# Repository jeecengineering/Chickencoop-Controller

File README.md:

# Chickencoop-Controller
Chickencoop controller (inactive)

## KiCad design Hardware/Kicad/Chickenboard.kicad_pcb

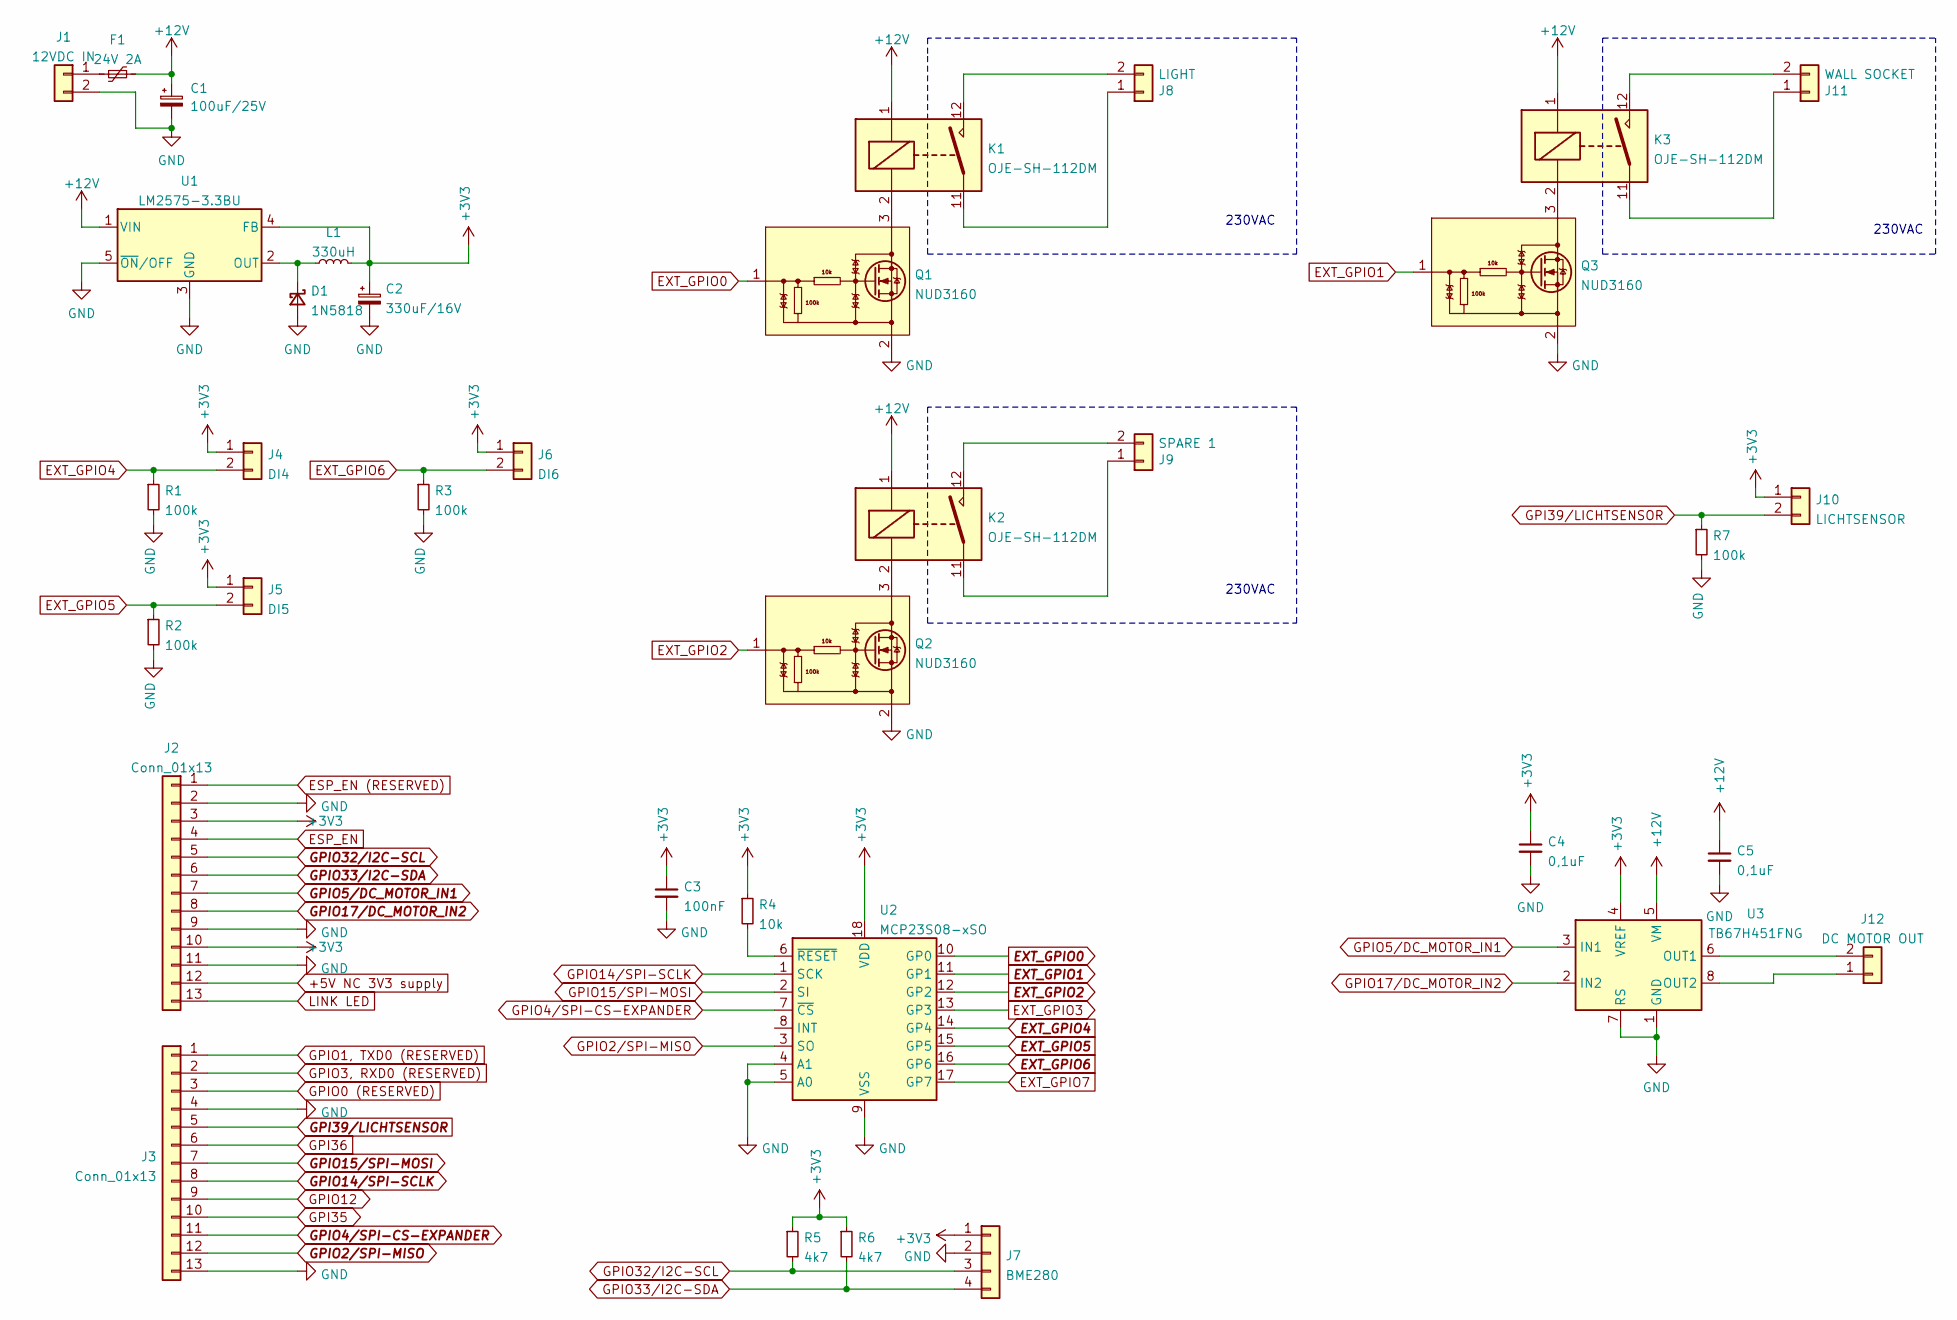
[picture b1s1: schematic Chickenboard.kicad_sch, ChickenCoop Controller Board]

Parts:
C1: 100uF/25V; CP_Radial_D8.0mm_P5.00mm
C2: 330uF/16V; CP_Radial_D8.0mm_P3.50mm
C3: 100nF; C_0805_2012Metric_Pad1.18x1.45mm_HandSolder
C4, C5: 0,1uF; C_0805_2012Metric_Pad1.18x1.45mm_HandSolder
D1: 1N5818; D_DO-41_SOD81_P10.16mm_Horizontal
F1: 24V 2A; Fuse_2920_7451Metric_Pad2.10x5.45mm_HandSolder
J1: 12VDC IN; TerminalBlock_CUIDevices_TB004_508-1x02_P5.08mm_Horizontal
J2, J3: Conn_01x13; PinSocket_1x13_P2.54mm_Vertical
J4: DI4; TerminalBlock_CUIDevices_TB004_508-1x02_P5.08mm_Horizontal
J5: DI5; TerminalBlock_CUIDevices_TB004_508-1x02_P5.08mm_Horizontal
J6: DI6; TerminalBlock_CUIDevices_TB004_508-1x02_P5.08mm_Horizontal
J7: BME280; TerminalBlock_CUIDevices_TB004_508-04BE-1x04_P5.08mm_Horizo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
J8: LIGHT; TerminalBlock_CUIDevices_TB004_508-1x02_P5.08mm_Horizontal
J9: SPARE 1; TerminalBlock_CUIDevices_TB004_508-1x02_P5.08mm_Horizontal
J10: LICHTSENSOR; TerminalBlock_CUIDevices_TB004_508-1x02_P5.08mm_Horizontal
J11: WALL SOCKET; TerminalBlock_CUIDevices_TB004_508-1x02_P5.08mm_Horizontal
J12: DC MOTOR OUT; TerminalBlock_CUIDevices_TB004_508-1x02_P5.08mm_Horizontal
K1, K2, K3: OJE-SH-112DM
L1: 330uH; L_Radial_D8.7mm_P5.00mm_Fastron_07HCP
Q1, Q2, Q3: NUD3160; SOT-23
R1, R2, R3, R7: 100k; R_0805_2012Metric_Pad1.20x1.40mm_HandSolder
R4: 10k; R_0805_2012Metric_Pad1.20x1.40mm_HandSolder
R5, R6: 4k7; R_0805_2012Metric_Pad1.20x1.40mm_HandSolder
U1: LM2575-3.3BU; TO-263-5_TabPin3
U2: MCP23S08-xSO; SOIC-18W_7.5x11.6mm_P1.27mm
U3: TB67H451FNG; HTSOP-8-1EP_3.9x4.9mm_P1.27mm_EP2.4x3.2mm_ThermalVias

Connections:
+3V3: C2.1, C3.1, C4.1, J2.3, J2.10, J4.1, J5.1, J6.1, J7.1, J10.1, L1.2, R4.1, R5.1, R6.1, U1.4 (FB), U2.18 (VDD), U3.4 (VREF)
+5V NC 3V3 supply: J2.12
+12V: C1.1, C5.1, F1.1, K1.1, K2.1, K3.1, U1.1 (VIN), U3.5 (VM)
ESP_EN: J2.4
ESP_EN (RESERVED): J2.1
EXT_GPIO0: Q1.1 (G), U2.10 (GP0)
EXT_GPIO1: Q3.1 (G), U2.11 (GP1)
EXT_GPIO2: Q2.1 (G), U2.12 (GP2)
EXT_GPIO3: U2.13 (GP3)
EXT_GPIO4: J4.2, R1.1, U2.14 (GP4)
EXT_GPIO5: J5.2, R2.1, U2.15 (GP5)
EXT_GPIO6: J6.2, R3.1, U2.16 (GP6)
EXT_GPIO7: U2.17 (GP7)
GND: C1.2, C2.2, C3.2, C4.2, C5.2, D1.2 (A), J1.2, J2.2, J2.9, J2.11, J3.4, J3.13, J7.2, Q1.2 (S), Q2.2 (S), Q3.2 (S), R1.2, R2.2, R3.2, R7.2, U1.3 (GND), U1.5 (~ON/OFF), U2.4 (A1), U2.5 (A0), U2.9 (VSS), U3.1 (GND), U3.7 (RS), U3.9 (GND)
GPI35: J3.10
GPI36: J3.6
GPI39/LICHTSENSOR: J3.5, J10.2, R7.1
GPIO0 (RESERVED): J3.3
GPIO1, TXD0 (RESERVED): J3.1
GPIO2/SPI-MISO: J3.12, U2.3 (SO)
GPIO3, RXD0 (RESERVED): J3.2
GPIO4/SPI-CS-EXPANDER: J3.11, U2.7 (~CS)
GPIO5/DC_MOTOR_IN1: J2.7, U3.3 (IN1)
GPIO12: J3.9
GPIO14/SPI-SCLK: J3.8, U2.1 (SCK)
GPIO15/SPI-MOSI: J3.7, U2.2 (SI)
GPIO17/DC_MOTOR_IN2: J2.8, U3.2 (IN2)
GPIO32/I2C-SCL: J2.5, J7.3, R5.2
GPIO33/I2C-SDA: J2.6, J7.4, R6.2
LINK LED: J2.13
unnamed: D1.1 (K), L1.1, U1.2 (OUT)
unnamed: F1.2, J1.1
unnamed: J8.1, K1.11
unnamed: J8.2, K1.12
unnamed: J9.1, K2.11
unnamed: J9.2, K2.12
unnamed: J11.1, K3.11
unnamed: J11.2, K3.12
unnamed: J12.1, U3.8 (OUT2)
unnamed: J12.2, U3.6 (OUT1)
unnamed: K1.2, Q1.3 (D)
unnamed: K2.2, Q2.3 (D)
unnamed: K3.2, Q3.3 (D)
unnamed: R4.2, U2.6 (~RESET)

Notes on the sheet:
230VAC

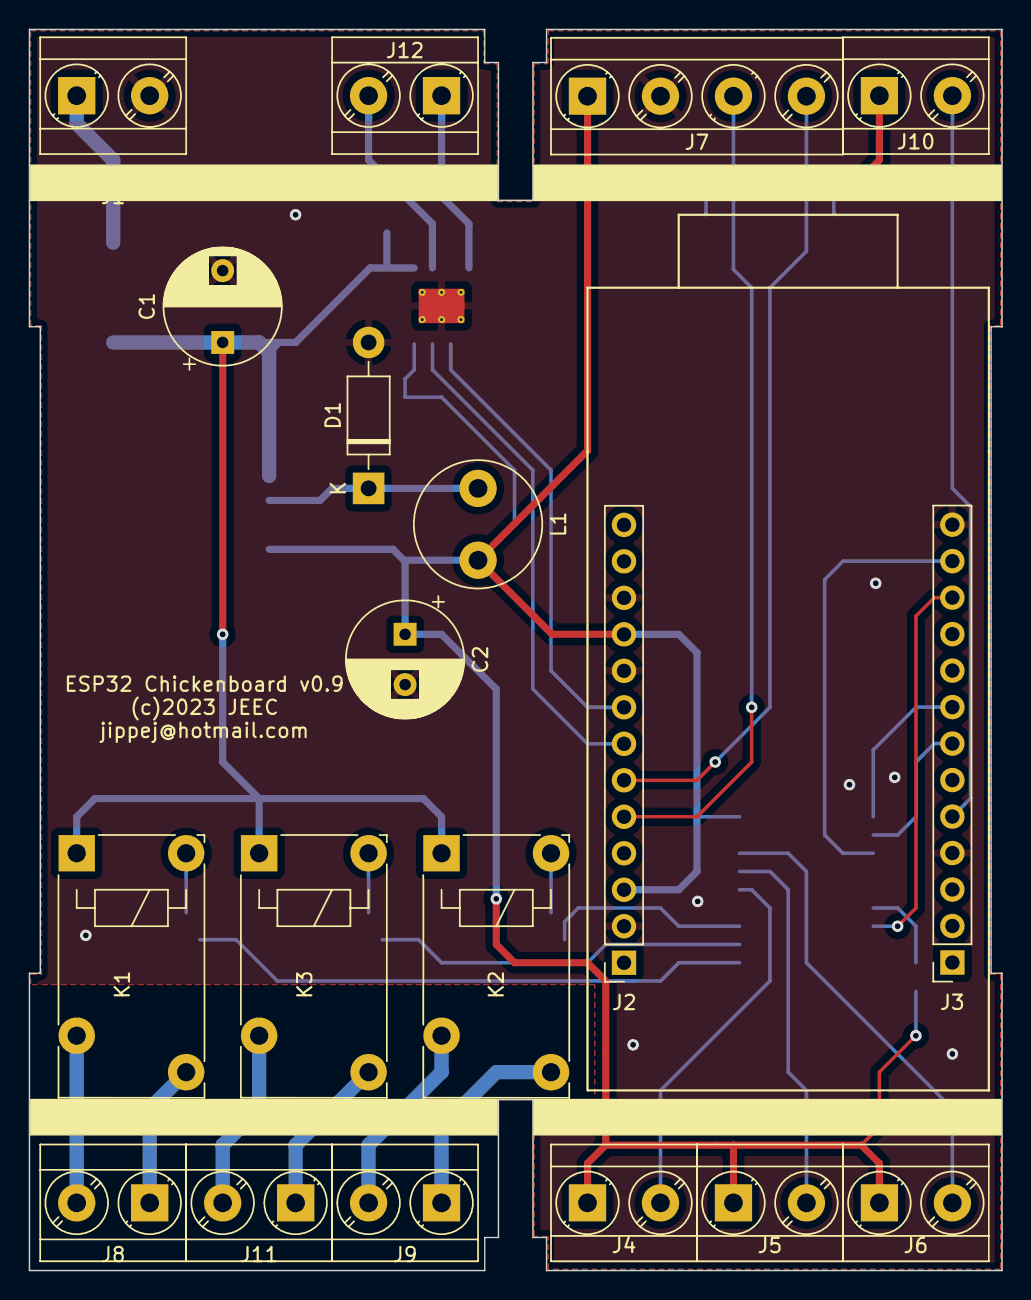
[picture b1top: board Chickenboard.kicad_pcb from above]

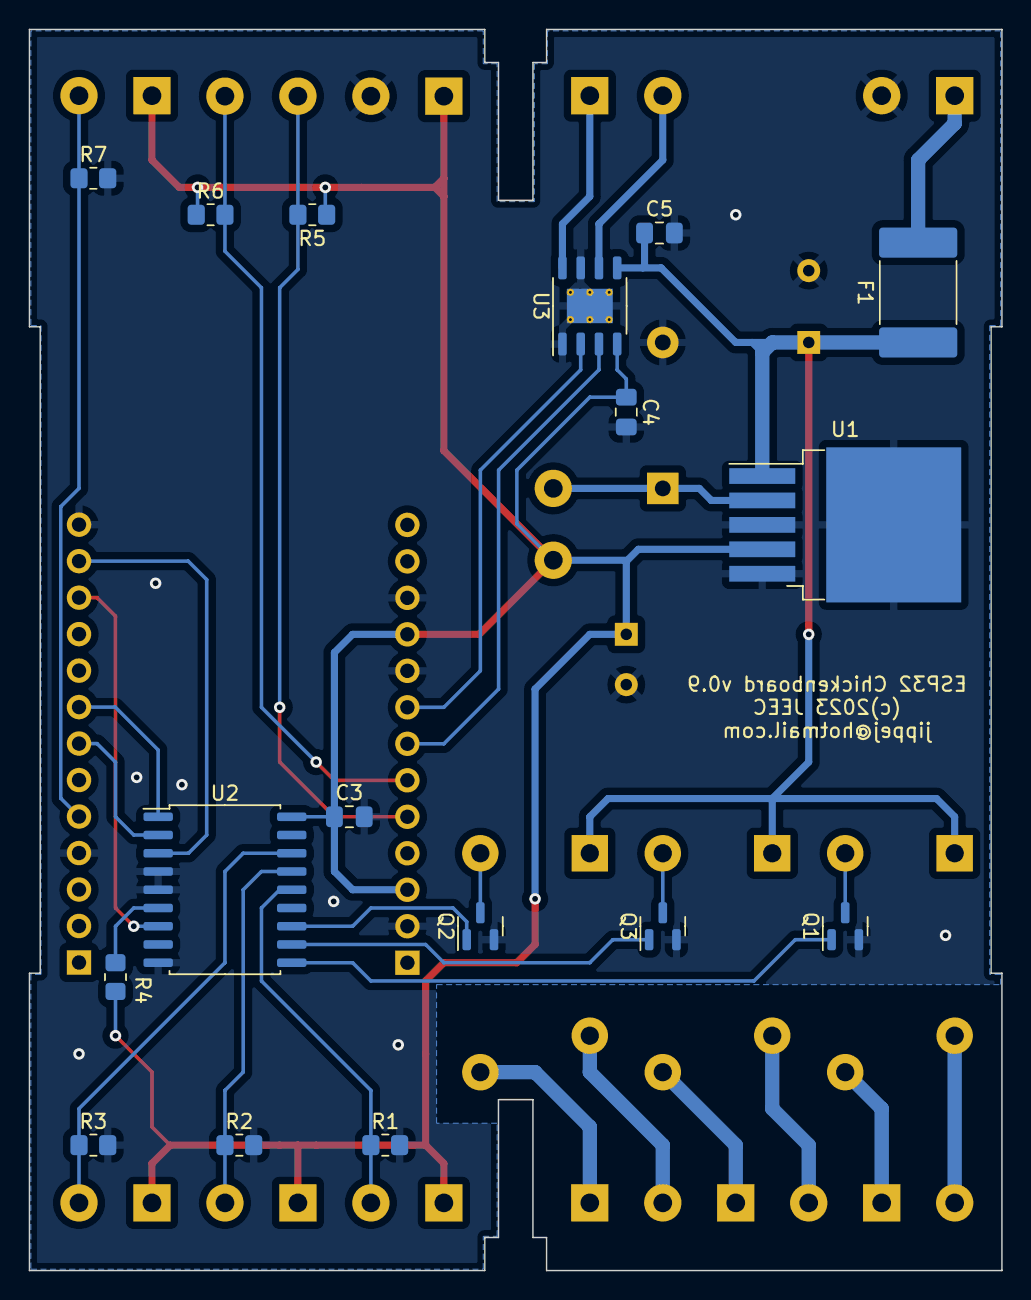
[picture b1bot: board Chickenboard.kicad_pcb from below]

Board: 2 copper layers, 67.7 x 86.4 mm, 36 parts (17 on the bottom side), 32 nets.

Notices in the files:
Hardware/Kicad/Chickenboard.kicad_pcb:
(c)2023 JEEC
